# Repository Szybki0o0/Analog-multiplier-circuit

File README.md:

# Analog Multiplier circuit

## Overview
The multiplier circuit presented in the schematic is an electronic system composed of several functional blocks working together to perform mathematical operations on input signals.

## Main Functional Blocks
The schematic consists of the following key sections:

1. **Power Supply (V+ and V-)**  
   - Voltage stabilization for the circuit.
   - Uses **MIC5207** for V+ regulation and **LT1054** as a charge pump for V-.

2. **Charge Pump**  
   - Responsible for generating the negative voltage required for some components.  
   - Utilizes **MCP6002** as an operational amplifier.
   - Utilizes **ADG779** as a CMOS switch.

3. **Voltage-Frequency Converter (VCF)**  
   - Based on **LM331N** operational amplifier, responsible for controlling the input signal through filtering.  
   - Includes adjustment via **RV1** potentiometer.

4. **Adding Offset**  
   - Allows adding a frequency shift to the input signal to allow correct operation with 0V.  
   - Implemented using **MCP6002**.

5. **Subtracting Offset**  
   - Compensates voltage by subtracting an offset value.  
   - Uses **MCP6002** and **RV2** potentiometer.

## How It Works
The circuit receives an input signal, which can be filtered and modified by adding or subtracting an offset. The processed signal is then transmitted to other circuit blocks where it can be used for further operations.

## Problems
VCF isn't working properly due to wrong choice of resistors and not enough current is flowing into integrated circuit.

## PCB
Physical implementation of a circuit:

## Author
Jakub Konior
Jakub Wiącek
Arkadiusz Kowalczyk

## Design Software
Designed using **KiCad EDA 8.0.2**.

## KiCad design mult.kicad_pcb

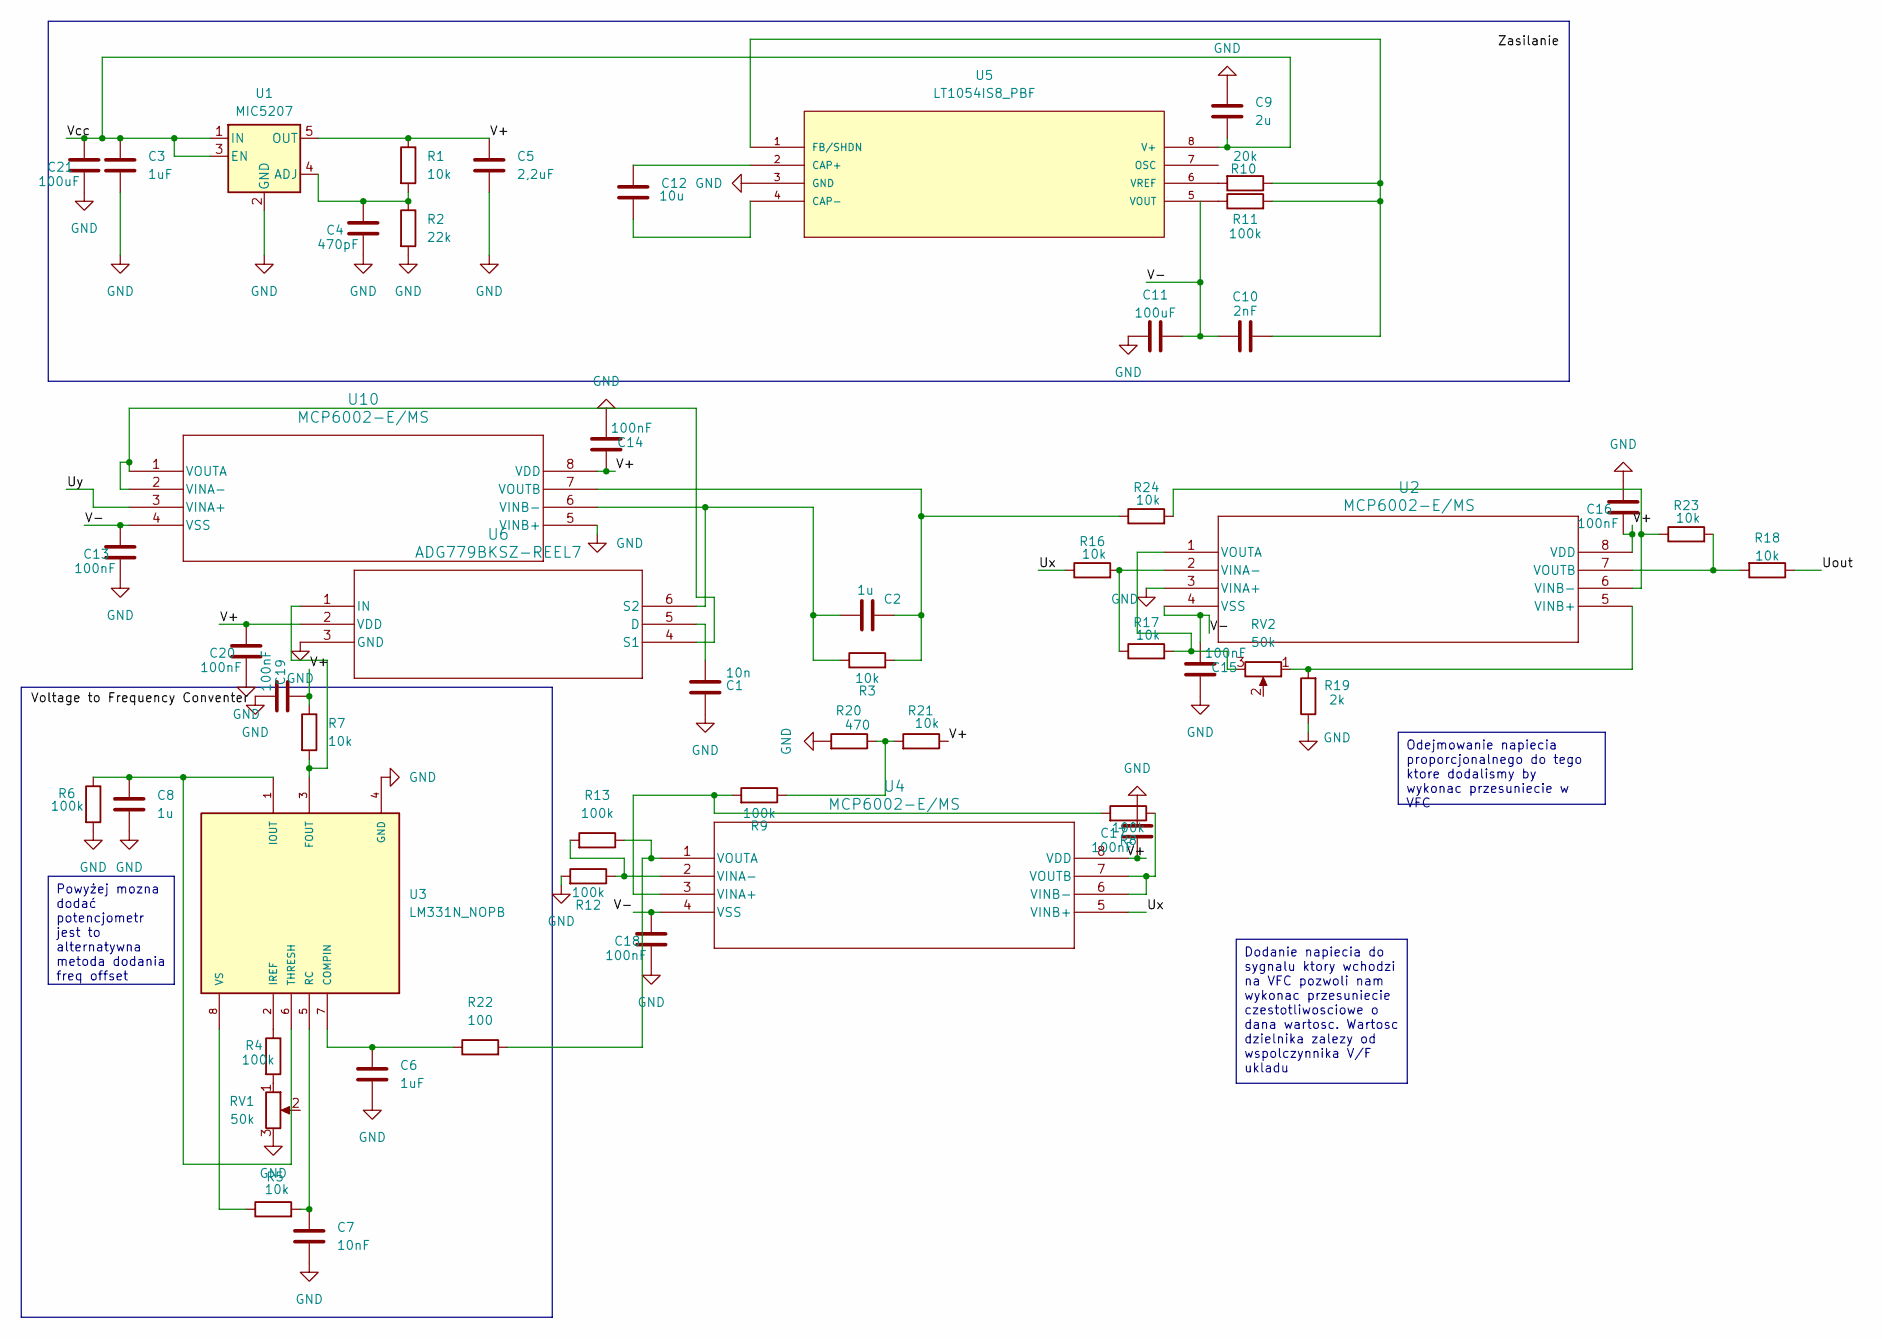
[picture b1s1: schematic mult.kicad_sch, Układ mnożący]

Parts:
C1: 10n; C_0805_2012Metric_Pad1.18x1.45mm_HandSolder
C2, C8: 1u; C_0805_2012Metric_Pad1.18x1.45mm_HandSolder
C3, C6: 1uF; C_0805_2012Metric_Pad1.18x1.45mm_HandSolder
C4: 470pF; C_0805_2012Metric_Pad1.18x1.45mm_HandSolder
C5: 2,2uF; C_0805_2012Metric_Pad1.18x1.45mm_HandSolder
C7: 10nF; CAP_B32529_02.5X06.5X07.3_TDK
C9: 2u; C_0805_2012Metric_Pad1.18x1.45mm_HandSolder
C10: 2nF; C_0805_2012Metric_Pad1.18x1.45mm_HandSolder
C11: 100uF; C_0805_2012Metric_Pad1.18x1.45mm_HandSolder
C12: 10u; C_0805_2012Metric_Pad1.18x1.45mm_HandSolder
C13, C14, C15, C16, C17, C18, C19, C20: 100nF; C_0805_2012Metric_Pad1.18x1.45mm_HandSolder
C21: 100uF; CP_EIA-3528-21_Kemet-B_Pad1.50x2.35mm_HandSolder
R1, R3, R5, R7, R16, R17, R18, R21, R23, R24: 10k; R_0805_2012Metric_Pad1.20x1.40mm_HandSolder
R2: 22k; R_0805_2012Metric_Pad1.20x1.40mm_HandSolder
R4, R6, R8, R9, R11, R12, R13: 100k; R_0805_2012Metric_Pad1.20x1.40mm_HandSolder
R10: 20k; R_0805_2012Metric_Pad1.20x1.40mm_HandSolder
R19: 2k; R_0805_2012Metric_Pad1.20x1.40mm_HandSolder
R20: 470; R_0805_2012Metric_Pad1.20x1.40mm_HandSolder
R22: 100; R_0805_2012Metric_Pad1.20x1.40mm_HandSolder
RV1, RV2: 50k; POT_3214W
U1: MIC5207; SOT-23-5
U2, U4, U10: MCP6002-E/MS; MSOP8_MC_MCH-L
U3: LM331N_NOPB; N08E_TEX; PARTREV 4040082/E 04/2010
U5: LT1054IS8_PBF; SO-8_S_LIT-L; MANUFACTURER_PART_NUMBER lt1054is8
U6: ADG779BKSZ-REEL7; KS_6_ADI-L

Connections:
/Uout: R18.1
/Ux: R16.1, U4.5 (VINB+)
/Uy: U10.3 (VINA+)
/V+: C5.1, C14.1, C16.2, C17.2, C19.1, C20.1, R1.1, R7.1, R21.1, U1.5 (OUT), U2.8 (VDD), U4.8 (VDD), U6.2 (VDD), U10.8 (VDD)
/V-: C10.1, C11.2, C13.1, C15.2, C18.1, U2.4 (VSS), U4.4 (VSS), U10.4 (VSS)
/Vcc: C3.1, C9.2, C21.1, U1.1 (IN), U1.3 (EN), U5.8 (V+)
GND: C1.2, C3.2, C4.2, C5.2, C6.2, C7.2, C8.2, C9.1, C11.1, C13.2, C14.2, C15.1, C16.1, C17.1, C18.2, C19.2, C20.2, C21.2, R2.2, R6.2, R12.2, R19.1, R20.2, RV1.3, U1.2 (GND), U2.3 (VINA+), U3.4 (GND), U5.3 (GND), U6.3 (GND), U10.5 (VINB+)
unnamed: R4.2, RV1.1
unnamed: R9.1, R20.1, R21.2
unnamed: C4.1, R1.2, R2.1, U1.4 (ADJ)
unnamed: R16.2, R17.1, U2.2 (VINA-)
unnamed 11: R19.2, RV2.1, U2.5 (VINB+); also elsewhere on the board
unnamed: R23.1, R24.2, U2.6 (VINB-)
unnamed 13: R17.2, RV2.3, U2.1 (VOUTA); also elsewhere on the board
unnamed: R18.2, R23.2, U2.7 (VOUTB)
unnamed: C6.1, R22.1, U3.7 (COMPIN)
unnamed: R7.2, U3.3 (FOUT), U6.1 (IN)
unnamed: C8.1, R6.1, U3.1 (IOUT), U3.6 (THRESH)
unnamed: R4.1, U3.2 (IREF)
unnamed: C7.1, R5.2, U3.5 (RC)
unnamed: R5.1, U3.8 (VS)
unnamed: R8.2, R9.2, U4.3 (VINA+)
unnamed: R12.1, R13.2, U4.2 (VINA-)
unnamed: R8.1, U4.6 (VINB-), U4.7 (VOUTB)
unnamed: R13.1, R22.2, U4.1 (VOUTA)
unnamed: C12.1, U5.2 (CAP+)
unnamed: C12.2, U5.4 (CAP-)
unnamed: C10.2, R10.1, R11.2, U5.1 (FB/SHDN)
unnamed: R11.1, U5.5 (VOUT)
unnamed: R10.2, U5.6 (VREF)
unnamed: C1.1, U6.5 (D)
unnamed: U6.4 (S1), U10.1 (VOUTA), U10.2 (VINA-)
unnamed: C2.1, R3.1, U6.6 (S2), U10.6 (VINB-)
unnamed: C2.2, R3.2, R24.1, U10.7 (VOUTB)

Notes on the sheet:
Dodanie napiecia do sygnalu ktory wchodzi na VFC pozwoli nam wykonac przesuniecie czestotliwosciowe o dana wartosc. Wartosc dzielnika zalezy od wspolczynnika V/F ukladu
Odejmowanie napiecia proporcjonalnego do tego ktore dodalismy by wykonac przesuniecie w VFC
Powyżej mozna dodać potencjometr jest to alternatywna metoda dodania freq offset

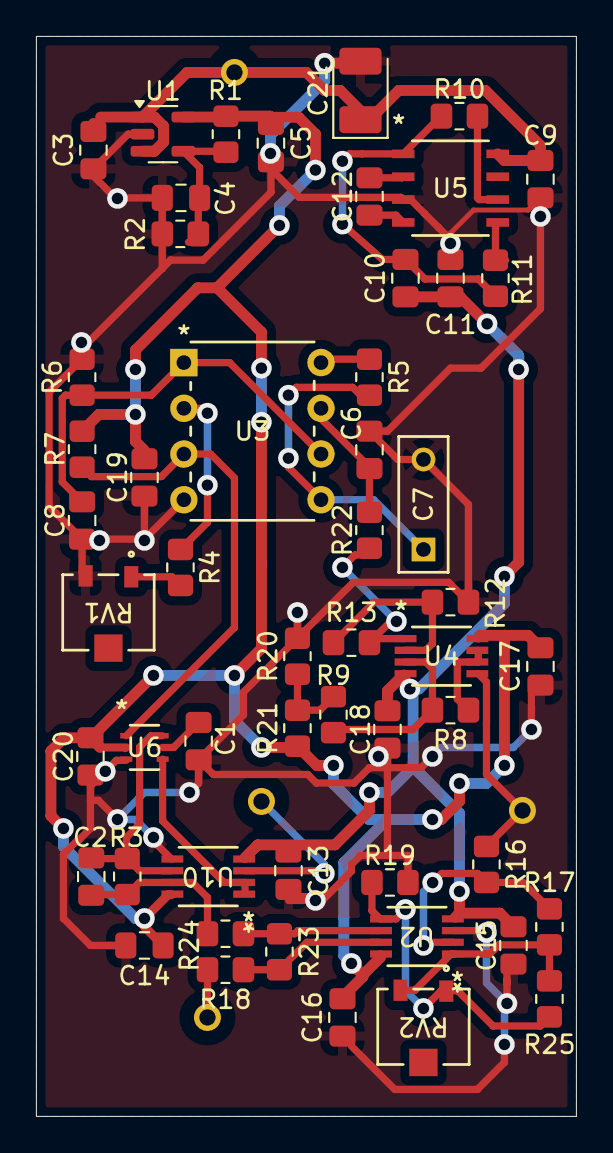
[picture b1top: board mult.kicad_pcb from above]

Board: 2 copper layers, 30.0 x 60.0 mm, 53 parts (0 on the bottom side), 32 nets.

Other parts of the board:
R25: 10k; R_0805_2012Metric_Pad1.20x1.40mm_HandSolder

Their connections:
unnamed 11: R25.2; also elsewhere on the board
unnamed 13: R25.1; also elsewhere on the board

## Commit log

2025-02-19 Upload of kicad project
